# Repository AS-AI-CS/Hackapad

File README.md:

**Hackapad**

This is a hackapad that executes common keyboard shortcuts on Macintosh computers such as the lock, and logout shortcuts. This macropad also executes some standard keyboard shortcuts such as copy and paste.

**Bill of Materials (BOM)**

- SEEDSTUDIO XIAO RP2040 x1
- MX-Style Switches x4
- Keycaps x4
- Custom PCB
- Bottom Shell (3D Printed)
- Top Shell (3D Printed)
- Glue (I will provide)
- OLED Display (Tentative, I may add an OLED to this project before ordering the PCB, depending on the kind of OLED recieved)

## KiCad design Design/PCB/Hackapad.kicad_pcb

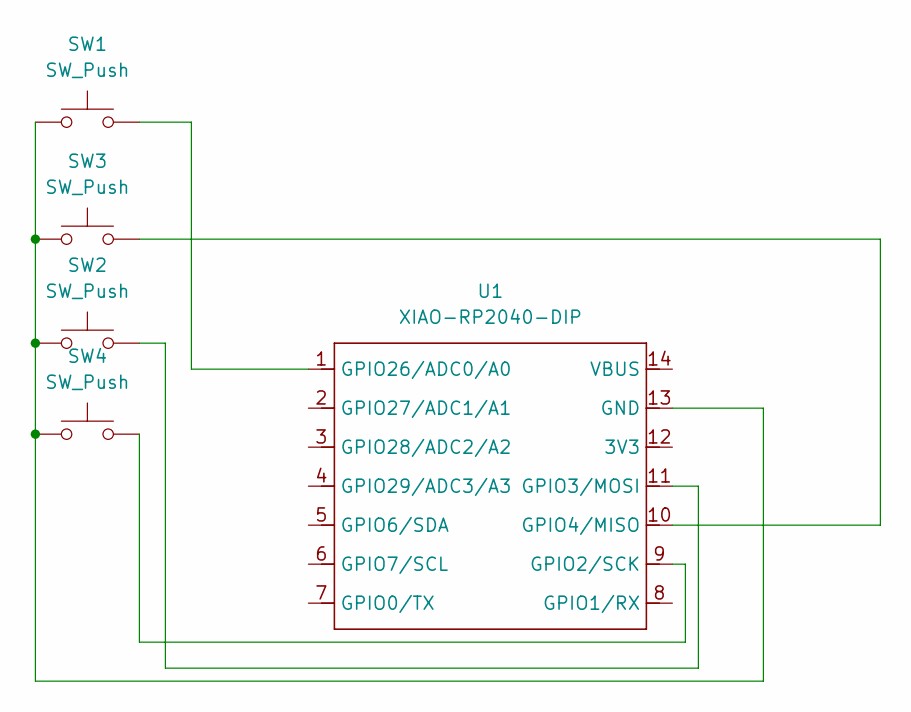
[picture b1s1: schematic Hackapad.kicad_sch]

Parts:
SW1, SW2, SW3, SW4: SW_Push; SW_Cherry_MX_1.00u_PCB
U1: XIAO-RP2040-DIP

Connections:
unnamed: SW1.1, SW2.1, SW3.1, SW4.1, U1.13 (GND)
unnamed: SW4.2, U1.9 (GPIO2/SCK)
unnamed: SW2.2, U1.11 (GPIO3/MOSI)
unnamed: SW3.2, U1.10 (GPIO4/MISO)
unnamed: SW1.2, U1.1 (GPIO26/ADC0/A0)

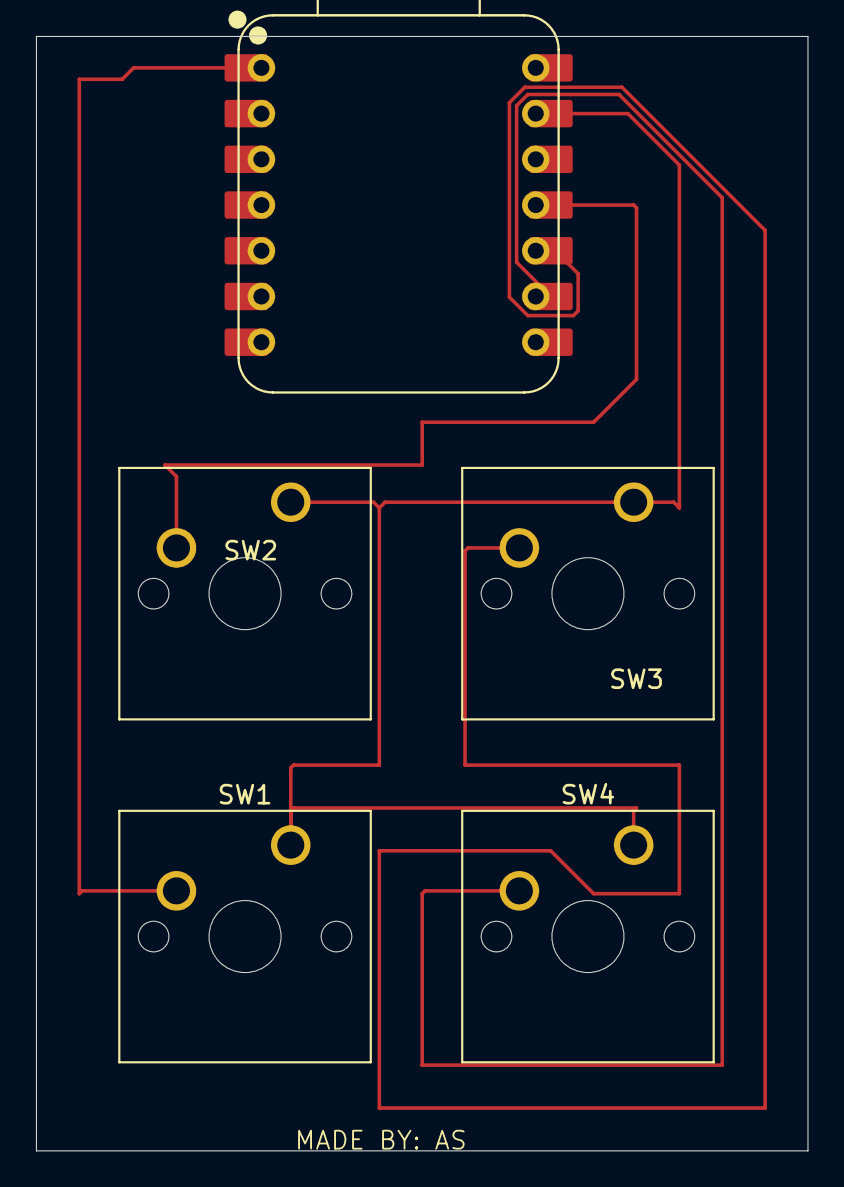
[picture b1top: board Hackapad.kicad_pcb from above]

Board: 2 copper layers, 42.9 x 61.9 mm, 5 parts (0 on the bottom side), 5 nets.
